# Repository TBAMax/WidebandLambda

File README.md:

# WidebandLambda

LSU4.9 conrtoller hardware based on Arduino Nano and Bosch CJ125 chip.
Has standard 18x2 character LCD display.
Can be used as standalone lambda monitor or as lambda controller for Speeduino.
Originally designed to be used with Speeduino.

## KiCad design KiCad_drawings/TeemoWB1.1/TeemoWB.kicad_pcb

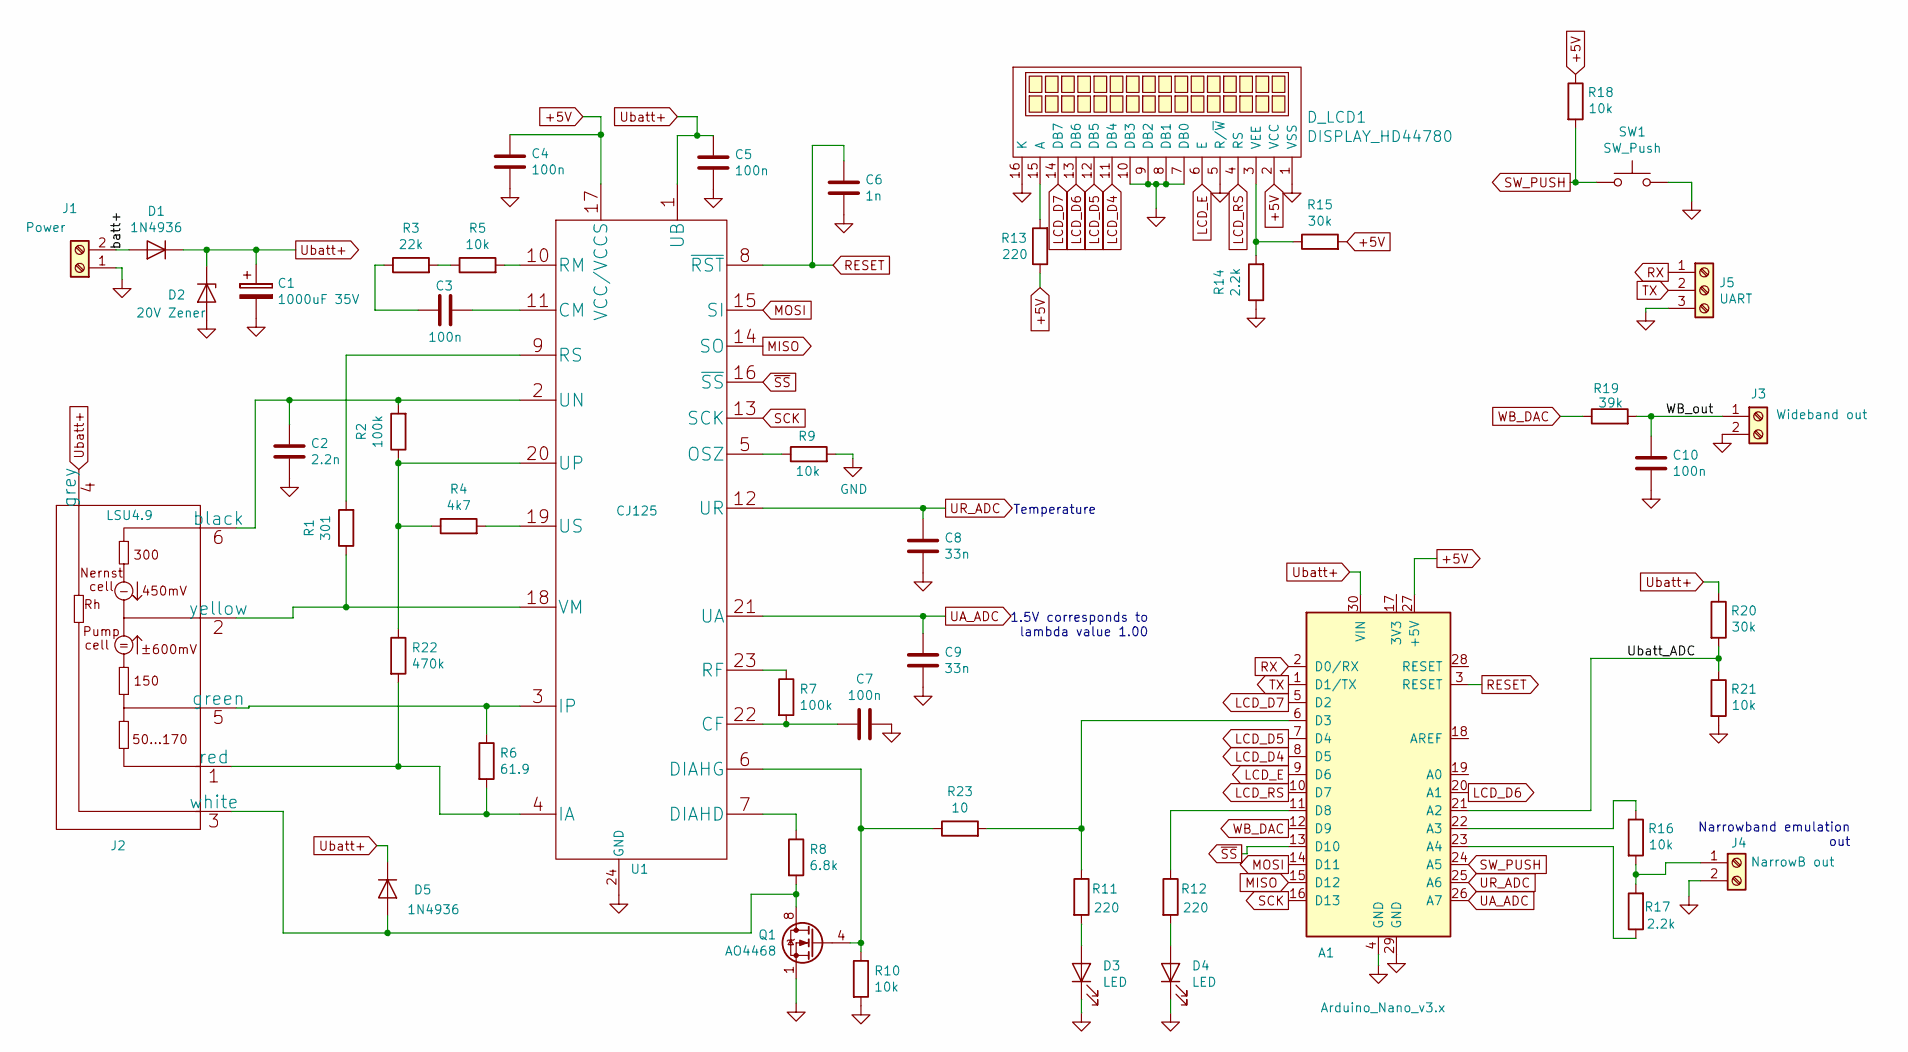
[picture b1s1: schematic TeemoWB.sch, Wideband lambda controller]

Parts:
A1: Arduino_Nano_v3.x; Arduino_Nano
C1: 1000uF 35V; CP_12.5x25mm_hor
C2: 2.2n; C_1206_3216Metric_Pad1.42x1.75mm_HandSolder
C3, C4, C5, C7, C10: 100n; C_1206_3216Metric_Pad1.42x1.75mm_HandSolder
C6: 1n; C_1206_3216Metric_Pad1.42x1.75mm_HandSolder
C8, C9: 33n; C_1206_3216Metric_Pad1.42x1.75mm_HandSolder
D1, D5: 1N4936; D_DO-41_SOD81_P7.62mm_Horizontal
D2: 20V Zener; D_DO-41_SOD81_P7.62mm_Horizontal
D3, D4: LED; LED_D5.0mm
D_LCD1: DISPLAY_HD44780; lcd_16x2_for_TBMAX_charger
J1: Power; TerminalBlock_Phoenix_MKDS-1,5-2-5.08_1x02_P5.08mm_Horizont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
J2: LSU4.9; TerminalBlock_Phoenix_MKDS-1,5-6-5.08_1x06_P5.08mm_Horizont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
J3: Wideband out; TerminalBlock_Phoenix_MKDS-1,5-2-5.08_1x02_P5.08mm_Horizont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
J4: NarrowB out; TerminalBlock_Phoenix_MKDS-1,5-2-5.08_1x02_P5.08mm_Horizont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
J5: UART; TerminalBlock_Phoenix_MKDS-1,5-3-5.08_1x03_P5.08mm_Horizont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
Q1: AO4468; SOIC-8_3.9x4.9mm_P1.27mm
R1: 301; R_1206_3216Metric
R2, R7: 100k; R_1206_3216Metric
R3: 22k; R_1206_3216Metric
R4: 4k7; R_1206_3216Metric
R5, R9, R10, R16, R18, R21: 10k; R_1206_3216Metric
R6: 61.9; R_1206_3216Metric
R8: 6.8k; R_1206_3216Metric
R11, R12, R13: 220; R_1206_3216Metric
R14, R17: 2.2k; R_1206_3216Metric
R15, R20: 30k; R_1206_3216Metric
R19: 39k; R_1206_3216Metric
R22: 470k; R_1206_3216Metric
R23: 10; R_1206_3216Metric
SW1: SW_Push; SW_PUSH_6mm_H7.3mm
U1: CJ125; SOIC-24W_7.5x15.4mm_P1.27mm

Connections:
+5V: A1.27 (+5V), C4.1, D_LCD1.2 (VCC), R13.1, R15.2, R18.1, U1.17 (VCC/VCCS)
/Ubatt_ADC: A1.21 (A2), R20.2, R21.1
/WB_out: C10.1, J3.1, R19.2
/batt+: D1.2 (A), J1.2
GND: A1.4 (GND), A1.29 (GND), C1.2, C2.2, C4.2, C5.2, C6.2, C7.2, C8.1, C9.1, C10.2, D2.2 (A), D3.1 (K), D4.1 (K), D_LCD1.1 (VSS), D_LCD1.5 (R/~W), D_LCD1.7 (DB0), D_LCD1.8 (DB1), D_LCD1.9 (DB2), D_LCD1.10 (DB3), D_LCD1.16 (K), J1.1, J3.2, J4.2, J5.3, Q1.1 (S), Q1.2 (S), Q1.3 (S), R9.2, R10.2, R14.1, R21.2, SW1.2, U1.24 (GND)
LCD_D4: A1.8 (D5), D_LCD1.11 (DB4)
LCD_D5: A1.7 (D4), D_LCD1.12 (DB5)
LCD_D6: A1.20 (A1), D_LCD1.13 (DB6)
LCD_D7: A1.5 (D2), D_LCD1.14 (DB7)
LCD_E: A1.9 (D6), D_LCD1.6 (E)
LCD_RS: A1.10 (D7), D_LCD1.4 (RS)
MISO: A1.15 (D12), U1.14 (SO)
MOSI: A1.14 (D11), U1.15 (SI)
unnamed: A1.6 (D3), R11.1, R23.2
unnamed: A1.11 (D8), R12.1
unnamed: A1.22 (A3), R16.1
unnamed: A1.23 (A4), R17.1
unnamed: C2.1, J2.6 (black), R2.2, U1.2 (UN)
unnamed: C3.1, R3.1
unnamed: C3.2, U1.11 (CM)
unnamed: C7.1, R7.2, U1.22 (CF)
unnamed: D3.2 (A), R11.2
unnamed: D4.2 (A), R12.2
unnamed: D5.2 (A), J2.3 (white), Q1.5 (D), Q1.6 (D), Q1.7 (D), Q1.8 (D), R8.2
unnamed: D_LCD1.3 (VEE), R14.2, R15.1
unnamed: D_LCD1.15 (A), R13.2
unnamed: J2.1 (red), R6.2, R22.2, U1.4 (IA)
unnamed: J2.2 (yellow), R1.1, U1.18 (VM)
unnamed: J2.5 (green), R6.1, U1.3 (IP)
unnamed: J4.1, R16.2, R17.2
unnamed: Q1.4 (G), R10.1, R23.1, U1.6 (DIAHG)
unnamed: R1.2, U1.9 (RS)
unnamed: R2.1, R4.1, R22.1, U1.20 (UP)
unnamed: R3.2, R5.1
unnamed: R4.2, U1.19 (US)
unnamed: R5.2, U1.10 (RM)
unnamed: R7.1, U1.23 (RF)
unnamed: R8.1, U1.7 (DIAHD)
unnamed: R9.1, U1.5 (OSZ)
RESET: A1.3 (RESET), C6.1, U1.8 (~RST)
RX: A1.2 (D0/RX), J5.1
SCK: A1.16 (D13), U1.13 (SCK)
SW_PUSH: A1.24 (A5), R18.2, SW1.1
TX: A1.1 (D1/TX), J5.2
UA_ADC: A1.26 (A7), C9.2, U1.21 (UA)
UR_ADC: A1.25 (A6), C8.2, U1.12 (UR)
Ubatt+: A1.30 (VIN), C1.1, C5.1, D1.1 (K), D2.1 (K), D5.1 (K), J2.4 (grey), R20.1, U1.1 (UB)
WB_DAC: A1.12 (D9), R19.1
~SS: A1.13 (D10), U1.16 (~SS)

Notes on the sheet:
Temperature
1.5V corresponds to lambda value 1.00
Narrowband emulation out

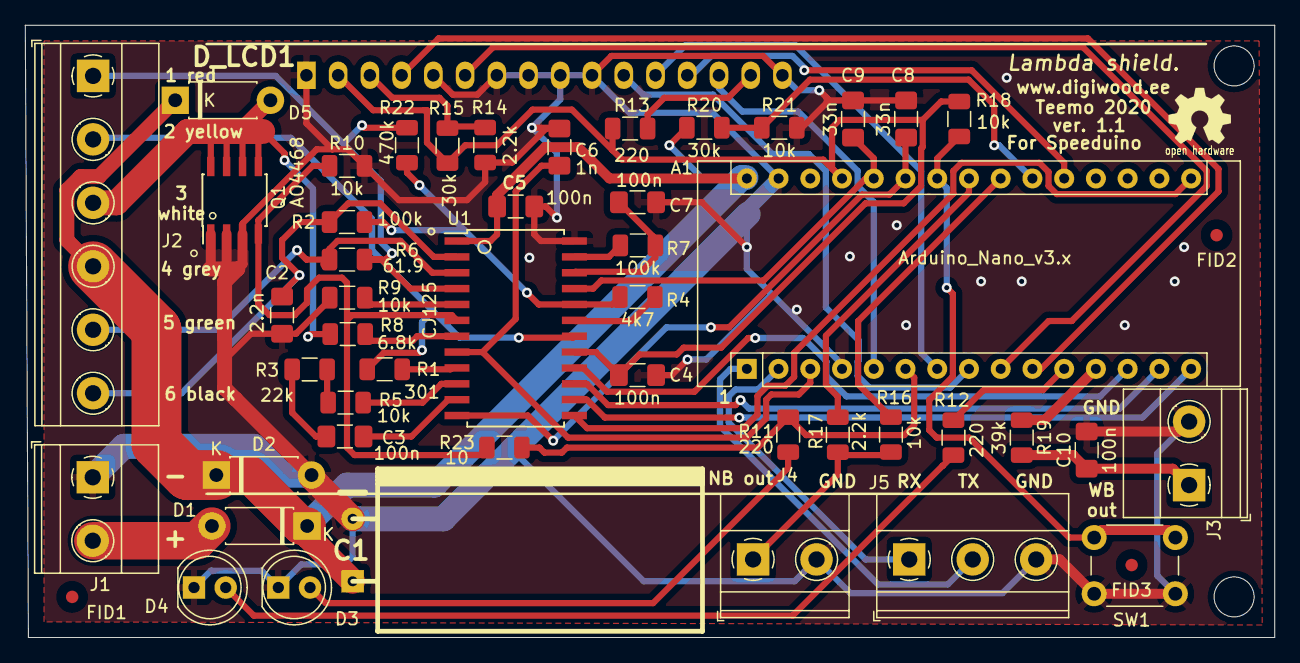
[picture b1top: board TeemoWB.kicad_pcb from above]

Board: 2 copper layers, 100.0 x 49.0 mm, 51 parts (0 on the bottom side), 49 nets.

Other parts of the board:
FID1, FID2, FID3: Fiducial_1mm_Dia_2.54mm_Outer_CopperTop

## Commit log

2020-08-08 Add schematics and board design files
2020-08-08 Add Arduino source code
